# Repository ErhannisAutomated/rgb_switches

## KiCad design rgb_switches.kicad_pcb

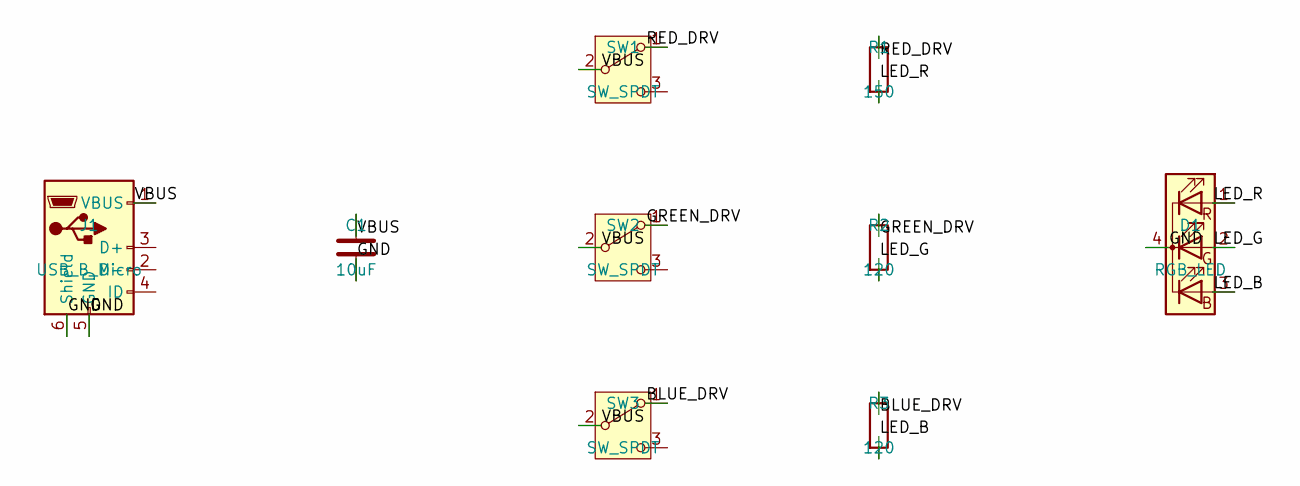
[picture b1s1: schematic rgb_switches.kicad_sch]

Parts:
C1: 10uF; C_0603_1608Metric; LCSC C19702
D1: RGB_LED; LED_RGB_Wuerth-PLCC4_3.2x2.8mm_150141M173100; LCSC C51933344
J1: USB_B_Micro; USB_Micro-B_Amphenol_10103594-0001LF_Horizontal; LCSC C10418
R1: 150; R_0603_1608Metric; LCSC C22808
R2, R3: 120; R_0603_1608Metric; LCSC C22787
SW1, SW2, SW3: SW_SPDT; SW_DPDT_CK_JS202011JCQN; LCSC C2681568

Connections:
BLUE_DRV: R3.1, SW3.1 (A)
GND: C1.2, D1.4 (K), J1.5 (GND), J1.6 (Shield)
GREEN_DRV: R2.1, SW2.1 (A)
LED_B: D1.3 (BA), R3.2
LED_G: D1.2 (GA), R2.2
LED_R: D1.1 (RA), R1.2
RED_DRV: R1.1, SW1.1 (A)
VBUS: C1.1, J1.1 (VBUS), SW1.2 (B), SW2.2 (B), SW3.2 (B)

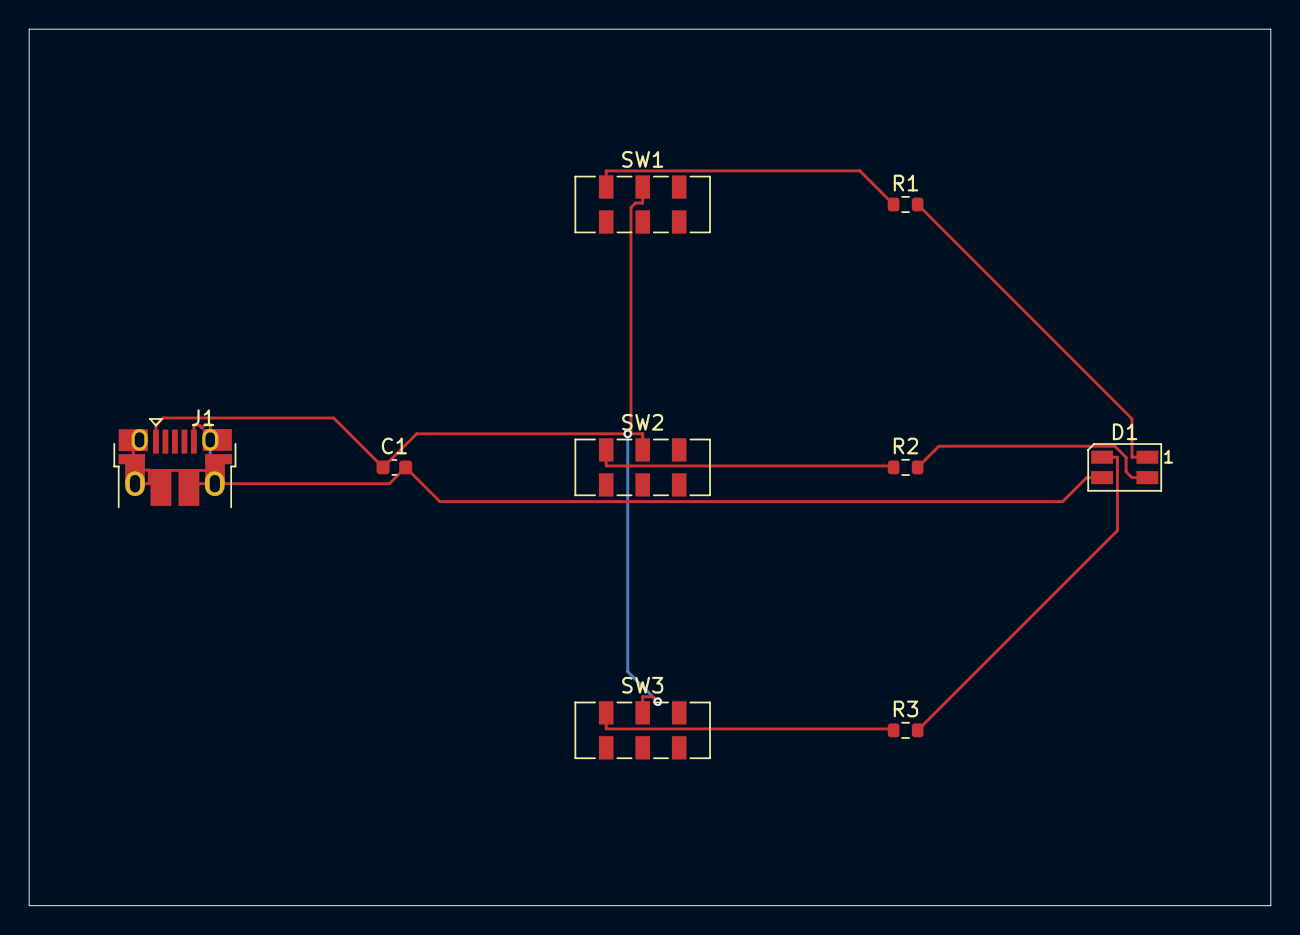
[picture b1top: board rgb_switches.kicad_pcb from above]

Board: 2 copper layers, 85.0 x 60.0 mm, 9 parts (0 on the bottom side), 8 nets.

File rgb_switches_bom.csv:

value,footprint,quantity,references,LCSC
10uF,Capacitor_SMD:C_0603_1608Metric,1,C1,
120,Resistor_SMD:R_0603_1608Metric,2,R3;R2,
SW_SPDT,Button_Switch_SMD:SW_DPDT_CK_JS202011JCQN,3,SW3;SW1;SW2,
RGB_LED,LED_SMD:LED_RGB_Wuerth-PLCC4_3.2x2.8mm_150141M173100,1,D1,
150,Resistor_SMD:R_0603_1608Metric,1,R1,
USB_B_Micro,Connector_USB:USB_Micro-B_Amphenol_10103594-0001LF_Horizontal,1,J1,

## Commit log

2026-05-06 Another test board; theoretically complete
2026-05-07 about to do a test
2026-05-07 dunno
